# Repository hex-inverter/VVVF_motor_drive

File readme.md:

# Three-Phase Induction Motor Controller

The inspiration for this project came from a very characteristic sound in Amsterdam metro trams. During acceleration or braking they make a "shifting gears" sound even though the motors are electric (this sound can also be heard in the demonstration video below).
I became interested in what causes this phenomenon and discovered that the sound is related to the switching behavior and frequency management of inverter-driven AC motors. To better understand these systems, I designed and built a complete three-phase induction motor controller and presented a project for seminar class as part of the course at Faculty of Electrical Engineering, University of Ljubljana.

The project focuses on generating variable-frequency three-phase waveforms using SPWM (Sinusoidal Pulse Width Modulation) and DDS (Direct Digital Synthesis) techniques implemented on an STM32 microcontroller. The controller is capable of driving an asynchronous motor directly from rectified mains voltage while allowing the motor speed to be controlled with a potentiometer.

Here you can find a video demonstration of the final product:

## Overview

The controller consists of a mains input stage with EMI filtering, a rectifier that generates a high-voltage DC bus, and a three-phase inverter built using IGBT transistors. The inverter is controlled by an STM32 microcontroller, which generates SPWM drive signals for the motor phases.
Motor speed is adjusted by a potentiometer, while the firmware continuously monitors current and DC bus voltage through ADC measurements. The project also implements different switching strategies to reduce transistor losses at higher output frequencies.

The more in-depth report of the working of the driver can be found in the project report (in Slovenian).

## Hardware

The hardware was designed in KiCad and PCB was etched at home.

Main components:
- EMI filtering
- Mains rectification
- Low-voltage auxiliary power supply
- Three-phase IGBT inverter
- Gate driver circuitry
- Current sensing
- STM32 control circuitry
- Custom PCB

## Firmware

The firmware is written for the STM32G030 microcontroller and generates three-phase SPWM signals for motor control. Frequency generation is implemented using DDS techniques and lookup tables, allowing smooth adjustment of motor speed and phase generation with 120° offsets between phases. The software also handles ADC measurements, frequency management, and inverter switching control.

## Repository Structure

```text
HW/             Hardware design files, schematics, PCB made in KiCad
FW/             STM32 firmware source code
docs/           Documentation and research papers
presentation/   Project report and presentation (sorry, it's in Slovenian)
```

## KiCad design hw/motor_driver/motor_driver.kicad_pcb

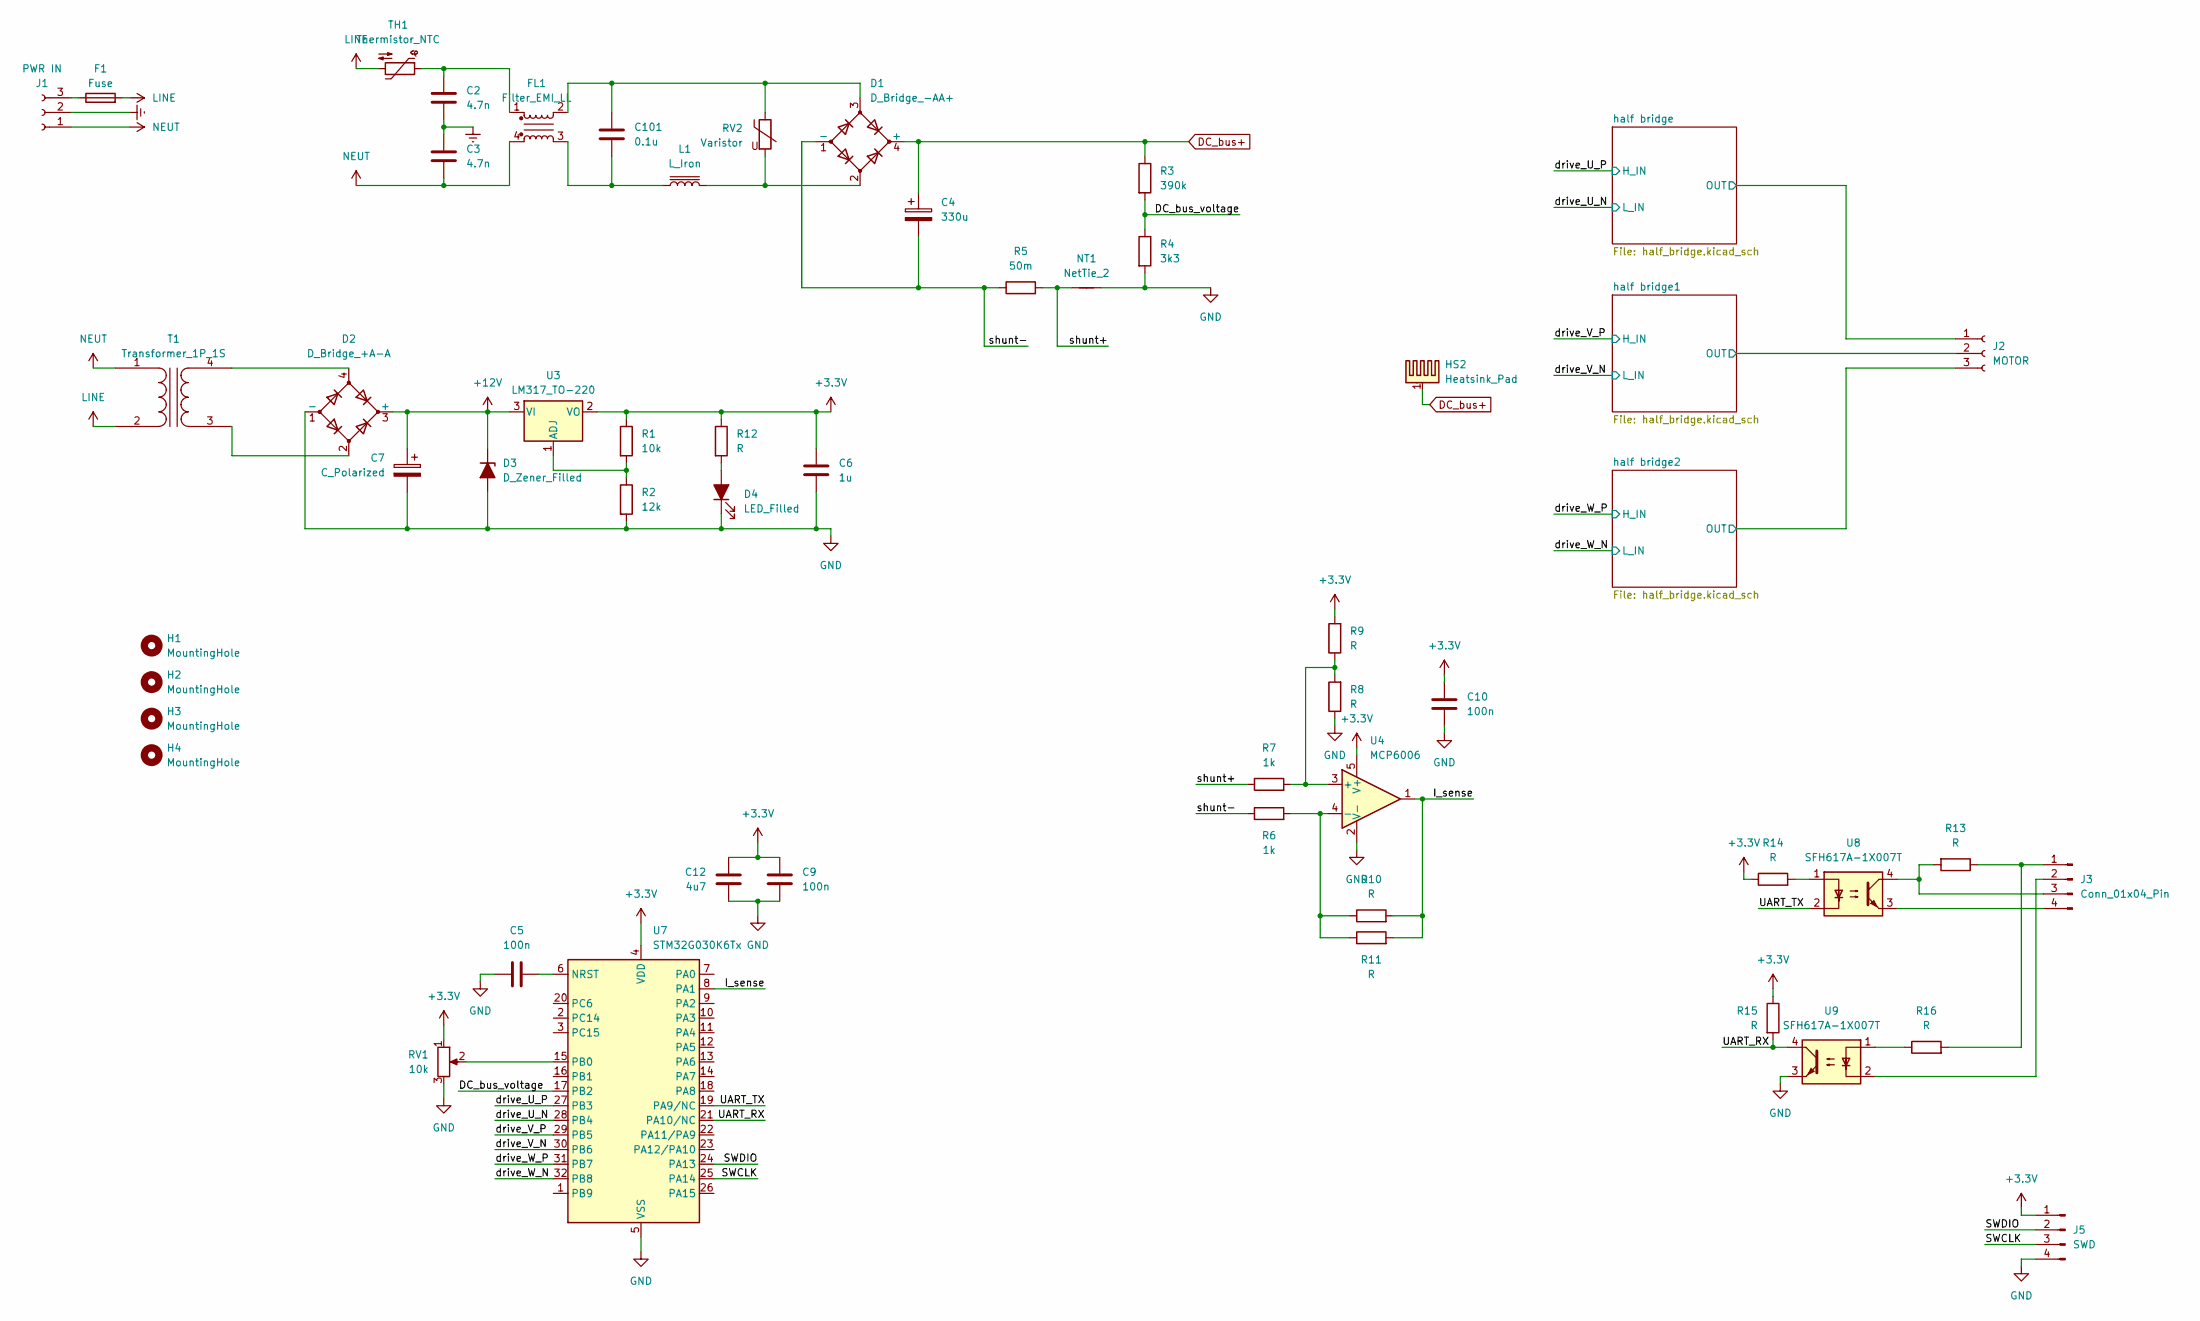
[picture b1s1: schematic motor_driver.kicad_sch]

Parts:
C2, C3: 4.7n; C_Rect_L13.0mm_W6.0mm_P10.00mm_FKS3_FKP3_MKS4
C4: 330u; CP_Radial_D30.0mm_P10.00mm_SnapIn
C5, C9, C10: 100n; C_0603_1608Metric_Pad1.08x0.95mm_HandSolder
C6: 1u; C_0603_1608Metric_Pad1.08x0.95mm_HandSolder
C7: C_Polarized; CP_Radial_D13.0mm_P5.00mm
C12: 4u7; C_0603_1608Metric_Pad1.08x0.95mm_HandSolder
C101: 0.1u; C_Rect_L19.0mm_W6.0mm_P15.00mm_MKS4
D1: D_Bridge_-AA+; Diode_Bridge_Vishay_KBL
D2: D_Bridge_+A-A; Diode_Bridge_19.0x3.5x10.0mm_P5.0mm
D3: D_Zener_Filled; D_MiniMELF_Handsoldering
D4: LED_Filled; LED_D5.0mm
F1: Fuse; Fuseholder_Cylinder-5x20mm_Stelvio-Kontek_PTF78_Horizontal_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
FL1: Filter_EMI_LL; L_CommonMode_Toroid_Vertical_L38.1mm_W20.3mm_Px15.24mm_Py22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
H1, H2, H3, H4: MountingHole; MountingHole_3.2mm_M3
HS2: Heatsink_Pad; heatsink_56x58
J1: PWR IN; TerminalBlock_Phoenix_MKDS-1,5-3-5.08_1x03_P5.08mm_Horizont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
J2: MOTOR; TerminalBlock_Phoenix_MKDS-1,5-3-5.08_1x03_P5.08mm_Horizont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
J3: Conn_01x04_Pin; PinHeader_1x04_P2.54mm_Vertical
J5: SWD; PinHeader_1x04_P2.54mm_Vertical
L1: L_Iron; Coil_40x48
NT1: NetTie_2; NetTie-2_SMD_Pad2.0mm
R1: 10k; R_0603_1608Metric_Pad0.98x0.95mm_HandSolder
R2: 12k; R_0603_1608Metric_Pad0.98x0.95mm_HandSolder
R3: 390k; R_Axial_DIN0411_L9.9mm_D3.6mm_P12.70mm_Horizontal
R4: 3k3; R_Axial_DIN0411_L9.9mm_D3.6mm_P12.70mm_Horizontal
R5: 50m; R_2512_6332Metric_Pad1.40x3.35mm_HandSolder
R6, R7: 1k; R_0603_1608Metric_Pad0.98x0.95mm_HandSolder
R8, R9, R10, R11, R12, R13, R14, R15, R16: R; R_0603_1608Metric_Pad0.98x0.95mm_HandSolder
RV1: 10k; PinSocket_1x03_P2.54mm_Vertical
RV2: Varistor; RV_Disc_D15.5mm_W4.9mm_P7.5mm
T1: Transformer_1P_1S; transformer_12V
TH1: Thermistor_NTC; C_Disc_D16.0mm_W5.0mm_P7.50mm
U3: LM317_TO-220; TO-220-3_Vertical
U4: MCP6006; TSOT-23-5_HandSoldering
U7: STM32G030K6Tx; LQFP-32_7x7mm_P0.8mm
U8, U9: SFH617A-1X007T; SMDIP-4_W9.53mm_Clearance8mm

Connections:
+3.3V: C6.1, C9.2, C10.2, C12.2, J5.1, R1.1, R9.2, R12.1, R14.1, R15.1, RV1.1, U3.2 (VO), U4.5 (V+), U7.4 (VDD)
+12V: C7.1, D2.3 (+), D3.1 (K), U3.3 (VI); also elsewhere on the board
/DC_bus_voltage: R3.2, R4.1, U7.17 (PB2)
/I_sense: R10.2, R11.2, U4.1, U7.8 (PA1)
/SWCLK: J5.3, U7.25 (PA14)
/SWDIO: J5.2, U7.24 (PA13)
/UART_RX: R15.2, U7.21 (PA10/NC), U9.4
/UART_TX: U7.19 (PA9/NC), U8.2
/drive_U_N: U7.28 (PB4); also elsewhere on the board
/drive_U_P: U7.27 (PB3); also elsewhere on the board
/drive_V_N: U7.30 (PB6); also elsewhere on the board
/drive_V_P: U7.29 (PB5); also elsewhere on the board
/drive_W_N: U7.32 (PB8); also elsewhere on the board
/drive_W_P: U7.31 (PB7); also elsewhere on the board
/half bridge1/OUT: J2.2; also elsewhere on the board
/half bridge2/OUT: J2.3; also elsewhere on the board
/half bridge/OUT: J2.1; also elsewhere on the board
/shunt+: NT1.1, R5.2, R7.1
/shunt-: C4.2, D1.1 (-), R5.1, R6.1
DC_bus+: C4.1, D1.4 (+), HS2.1, R3.1; also elsewhere on the board
Earth: C2.2, C3.1, J1.2
GND: C5.1, C6.2, C7.2, C9.1, C10.1, C12.1, D2.1 (-), D3.2 (A), D4.1 (K), J5.4, NT1.2, R2.2, R4.2, R8.1, RV1.3, U4.2 (V-), U7.5 (VSS), U9.3; also elsewhere on the board
LINE: F1.2, T1.2 (AB), TH1.2
NEUT: C3.2, FL1.4, J1.1, T1.1 (AA)
unnamed: C2.1, FL1.1, TH1.1
unnamed: C101.1, D1.3, FL1.2, RV2.1
unnamed: C101.2, FL1.3, L1.1
unnamed: D1.2, L1.2, RV2.2
unnamed: D4.2 (A), R12.2
unnamed: F1.1, J1.3
unnamed: J3.1, R13.1, R16.2
unnamed: J3.2, U9.2
unnamed: J3.3, R13.2, U8.4
unnamed: J3.4, U8.3
unnamed: R14.2, U8.1
unnamed: R16.1, U9.1
unnamed: D2.2, T1.3 (SA)
unnamed: D2.4, T1.4 (SB)
unnamed: R1.2, R2.1, U3.1 (ADJ)
unnamed: R7.2, R8.2, R9.1, U4.3 (+)
unnamed: R6.2, R10.1, R11.1, U4.4 (-)
unnamed: C5.2, U7.6 (NRST)
unnamed: RV1.2, U7.15 (PB0)

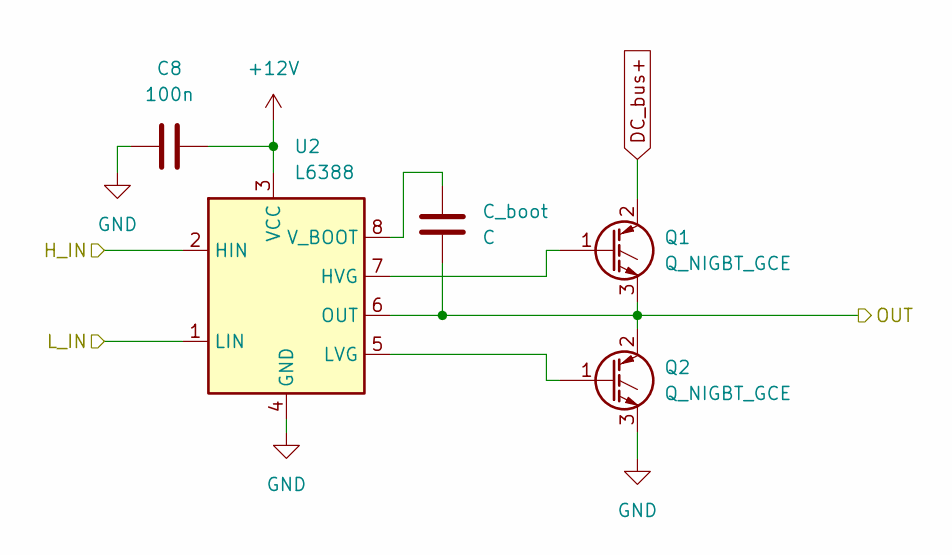
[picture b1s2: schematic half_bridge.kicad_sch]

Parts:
C8: 100n; C_0603_1608Metric_Pad1.08x0.95mm_HandSolder
C_boot: C; C_0603_1608Metric_Pad1.08x0.95mm_HandSolder
Q1, Q2: Q_NIGBT_GCE; TO-220-3_Vertical
U2: L6388; SO-8_3.9x4.9mm_P1.27mm

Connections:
+12V: C8.2, U2.3 (VCC); also elsewhere on the board
/drive_U_N: U2.1 (LIN); also elsewhere on the board
/drive_U_P: U2.2 (HIN); also elsewhere on the board
/half bridge/OUT: Q1.3 (E), Q2.2 (C), U2.6 (OUT); also elsewhere on the board
DC_bus+: Q1.2 (C); also elsewhere on the board
GND: C8.1, Q2.3 (E), U2.4 (GND); also elsewhere on the board
unnamed: Q1.1 (G), U2.7 (HVG)
unnamed: Q2.1 (G), U2.5 (LVG)
unnamed 44: U2.8 (V_BOOT); also elsewhere on the board

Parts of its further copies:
C13, C14: 100n; C_0603_1608Metric_Pad1.08x0.95mm_HandSolder
C_boot1, C_boot2, C_boot3: C; C_0603_1608Metric_Pad1.08x0.95mm_HandSolder
Q3, Q4, Q5, Q6: Q_NIGBT_GCE; TO-220-3_Vertical
U5, U6: L6388; SO-8_3.9x4.9mm_P1.27mm

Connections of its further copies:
+12V: C13.2, C14.2, U5.3 (VCC), U6.3 (VCC); also elsewhere on the board
/drive_V_N: U5.1 (LIN); also elsewhere on the board
/drive_V_P: U5.2 (HIN); also elsewhere on the board
/drive_W_N: U6.1 (LIN); also elsewhere on the board
/drive_W_P: U6.2 (HIN); also elsewhere on the board
/half bridge1/OUT: C_boot2.2, Q3.3 (E), Q4.2 (C), U5.6 (OUT); also elsewhere on the board
/half bridge2/OUT: C_boot3.2, Q5.3 (E), Q6.2 (C), U6.6 (OUT); also elsewhere on the board
/half bridge/OUT: C_boot1.2; also elsewhere on the board
DC_bus+: Q3.2 (C), Q5.2 (C); also elsewhere on the board
GND: C13.1, C14.1, Q4.3 (E), Q6.3 (E), U5.4 (GND), U6.4 (GND); also elsewhere on the board
unnamed: Q3.1 (G), U5.7 (HVG)
unnamed: Q4.1 (G), U5.5 (LVG)
unnamed: Q5.1 (G), U6.7 (HVG)
unnamed: Q6.1 (G), U6.5 (LVG)
unnamed 44: C_boot1.1; also elsewhere on the board
unnamed: C_boot2.1, U5.8 (V_BOOT)
unnamed: C_boot3.1, U6.8 (V_BOOT)

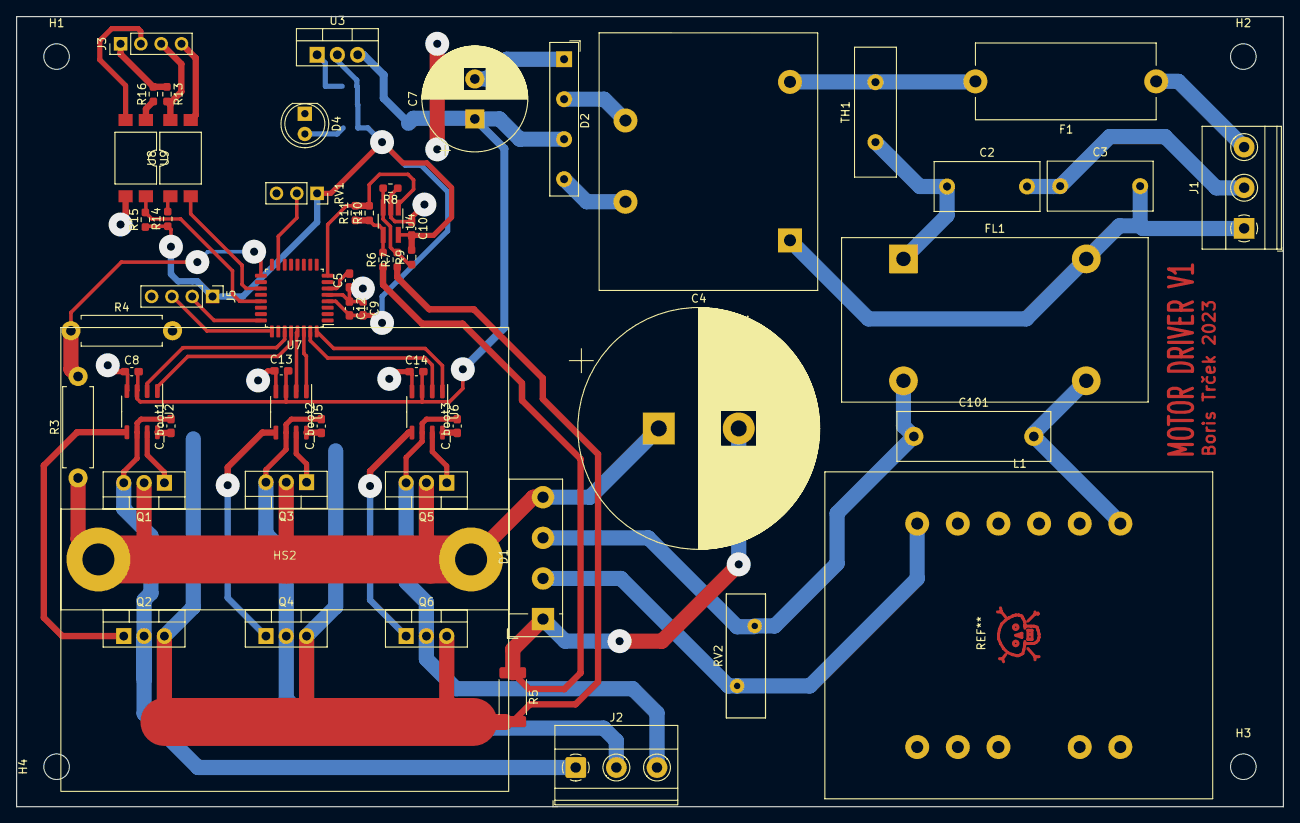
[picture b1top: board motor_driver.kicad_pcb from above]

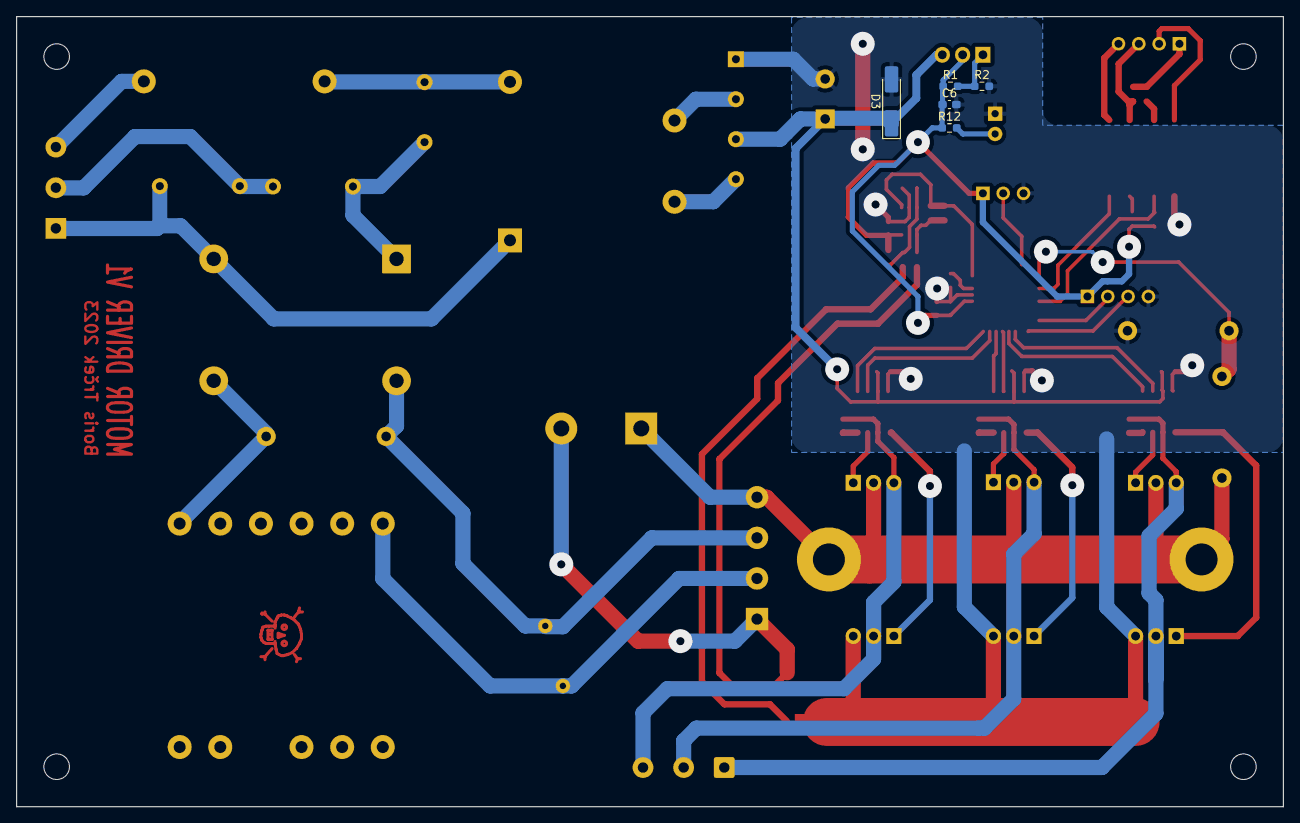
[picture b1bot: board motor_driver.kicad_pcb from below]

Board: 2 copper layers, 158.4 x 98.8 mm, 67 parts (5 on the bottom side), 52 nets.

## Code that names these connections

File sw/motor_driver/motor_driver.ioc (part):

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Mcu.Name=STM32G030K(6-8)Tx
Mcu.Package=LQFP32
Mcu.UserName=STM32G030K6Tx
PA1.GPIOParameters=GPIO_Label
PA1.GPIO_Label=I_MEAS
PA1.Mode=IN1
PA1.Signal=ADC1_IN1
PA13.Mode=Serial_Wire
PA13.Signal=SYS_SWDIO
PA14-BOOT0.Mode=Serial_Wire
PA14-BOOT0.Signal=SYS_SWCLK
PB0.GPIOParameters=GPIO_Label
PB0.GPIO_Label=POT
PB0.Mode=IN8
PB0.Signal=ADC1_IN8
PB1.GPIOParameters=GPIO_Label
PB1.GPIO_Label=TRIG
PB1.Signal=GPIO_Output
PB2.GPIOParameters=GPIO_Label
PB2.GPIO_Label=V_MEAS
PB2.Mode=IN10
PB2.Signal=ADC1_IN10
PB3.GPIOParameters=GPIO_Label
PB3.GPIO_Label=U_H
PB3.Signal=GPIO_Output
PB4.GPIOParameters=PinState,GPIO_Label
PB4.GPIO_Label=U_L
PB4.PinState=GPIO_PIN_SET
PB4.Signal=GPIO_Output
PB5.GPIOParameters=GPIO_Label
PB5.GPIO_Label=V_H
PB5.Signal=GPIO_Output
PB6.GPIOParameters=GPIO_Label
PB6.GPIO_Label=DEAD
PB6.Signal=GPIO_Analog
PB7.GPIOParameters=GPIO_Label
PB7.GPIO_Label=W_H
PB7.Signal=GPIO_Output
PB8.GPIOParameters=PinState,GPIO_Label,GPIO_FM8
PB8.GPIO_FM8=__NULL
PB8.GPIO_Label=W_L
PB8.PinState=GPIO_PIN_SET
PB8.Signal=GPIO_Output
PB9.GPIOParameters=GPIO_Label
PB9.GPIO_Label=V_L
PB9.Signal=GPIO_Output
RCC.HSE_VALUE=8000000
RCC.SYSCLKFreq_VALUE=64000000
RCC.SYSCLKSource=RCC_SYSCLKSOURCE_PLLCLK
board=custom

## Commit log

2023-09-24 finished PCB
2023-09-28 Added software
2023-10-02 first working version
2026-05-17 added presentation, minor changes
2026-05-17 added readme, improved gitignore
